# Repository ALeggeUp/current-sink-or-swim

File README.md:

# Current Sink or Swim (CSOS)

Project work from The Online Electronics Aprenticeship program at [Contextual Electronics](https://contextualelectronics.com/)

# License

This work is licensed under the Creative Commons Attribution 4.0 International License. To view a copy of this license, visit http://creativecommons.org/licenses/by/4.0/ or send a letter to Creative Commons, PO Box 1866, Mountain View, CA 94042, USA.

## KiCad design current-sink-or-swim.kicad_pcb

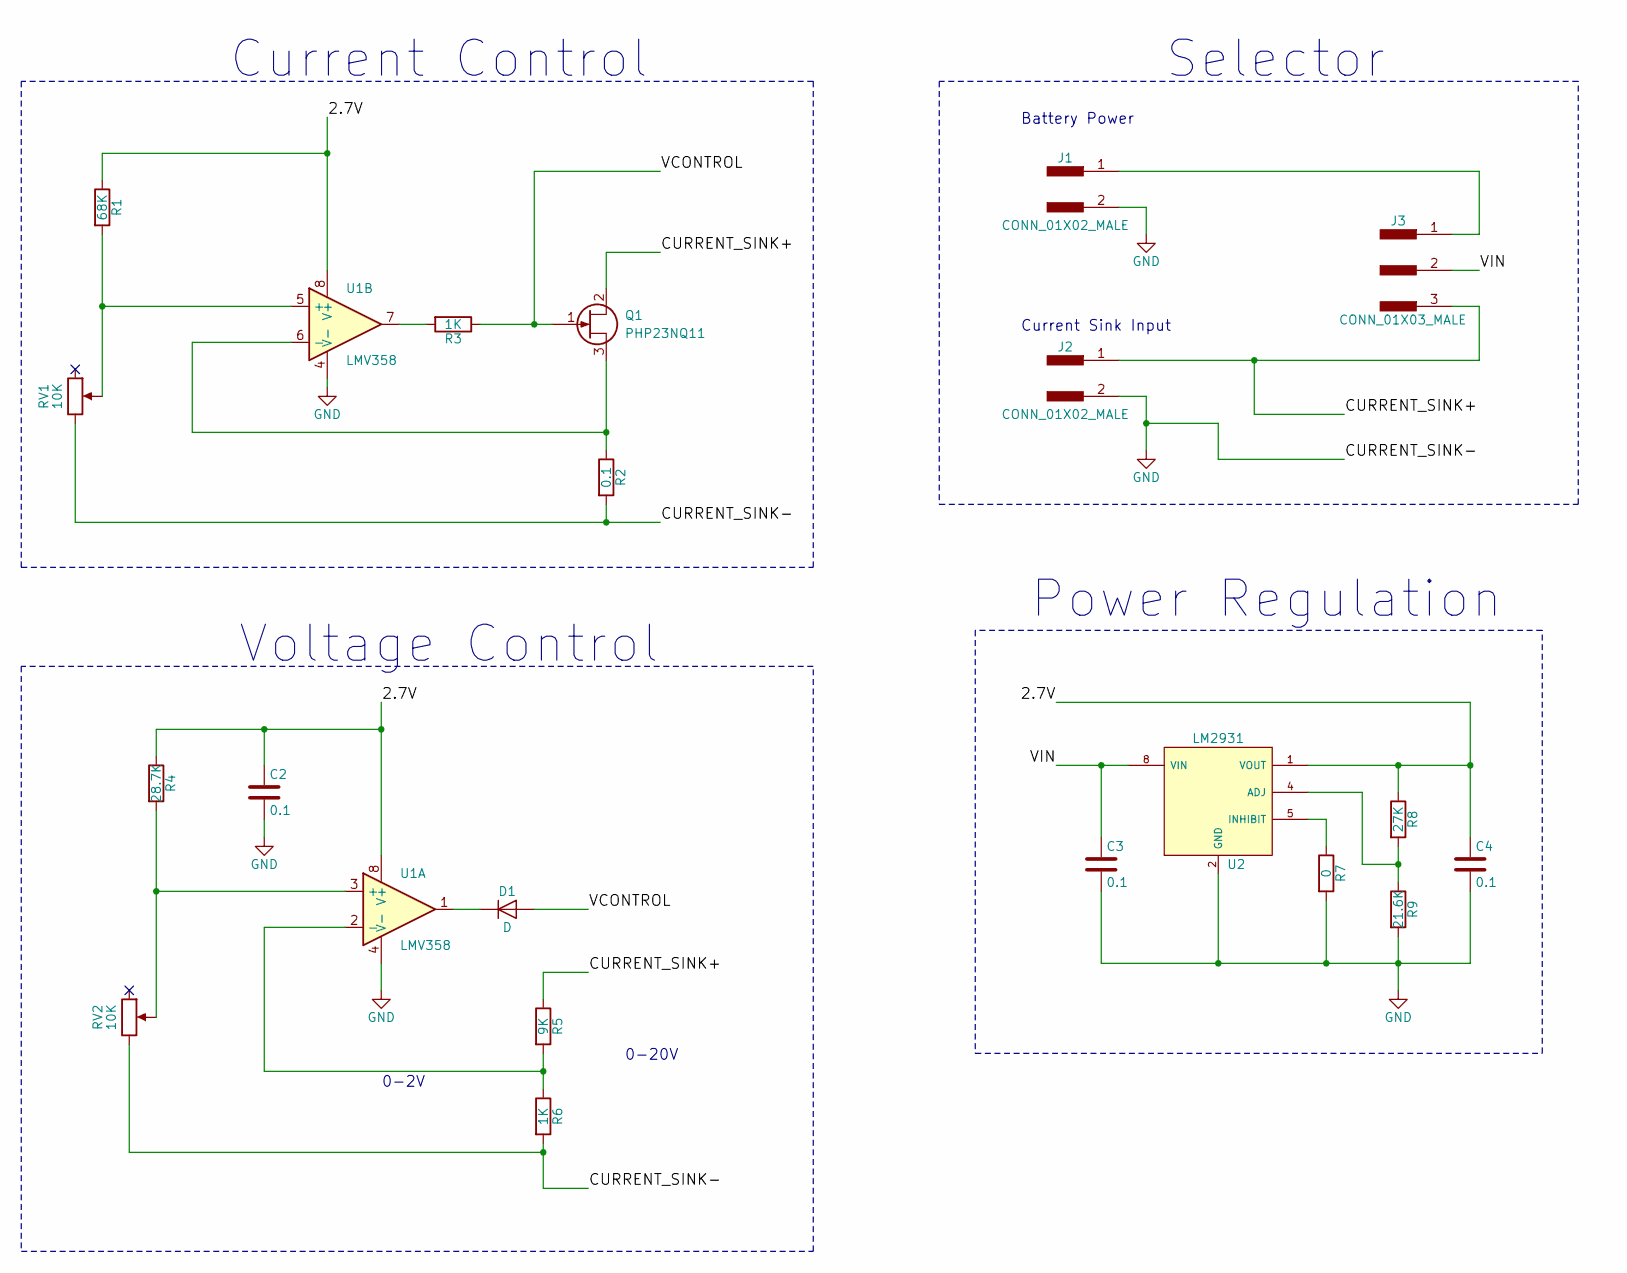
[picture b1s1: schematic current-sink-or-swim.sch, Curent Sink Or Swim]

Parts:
C2, C3, C4: 0.1; C_0805_HandSoldering
D1: D; D_SOD-123; MPN 1N4148W-TP
J1, J2: CONN_01X02_MALE; TerminalBlock_Pheonix_PT-5mm_2pol; MPN 1792863
J3: CONN_01X03_MALE; Pin_Header_Straight_1x03_Pitch2.54mm
Q1: PHP23NQ11; TO-220_Vertical; MPN PHP23NQ11T,127
R1: 68K; R_0805_HandSoldering; MPN RC0805JR-0768KL
R2: 0.1; R_Axial_DIN0414_L11.9mm_D4.5mm_P15.24mm_Horizontal; MPN AC01000001007JA100
R3, R6: 1K; R_0805_HandSoldering; MPN RC0805JR-071KL
R4: 28.7K; R_0805_HandSoldering; MPN RC0805FR-0728K7L
R5: 9K; R_0805_HandSoldering; MPN RC0805FR-079K09L
R7: 0; R_0805_HandSoldering; MPN RC0805JR-070RL
R8: 27K; R_0805_HandSoldering; MPN RC0805FR-0727KL
R9: 21.6K; R_0805_HandSoldering; MPN RC0805FR-0721K5L
RV1, RV2: 10K; P090L-02F25BR10K
U1: LMV358; SOIC-8_3.9x4.9mm_Pitch1.27mm
U2: LM2931; SOIC-8_3.9x4.9mm_Pitch1.27mm; MPN LM2931CDR2G

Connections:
/2.7V: C2.1, C4.1, R1.1, R4.1, R8.1, U1.8 (V+), U2.1 (VOUT); also elsewhere on the board
/CURRENT_SINK+: J2.1, J3.3, Q1.2 (D), R5.1
/VCONTROL: D1.2 (A), Q1.1 (G), R3.1
/VIN: C3.1, J3.2, U2.8 (VIN)
GND: C2.2, C3.2, C4.2, J1.2, J2.2, R2.2, R6.2, R7.2, R9.2, RV1.3, RV2.3, U1.4 (V-), U2.2 (GND), U2.3 (GND), U2.6 (GND), U2.7 (GND); also elsewhere on the board
unnamed: D1.1 (K), U1.1
unnamed: J1.1, J3.1
unnamed: Q1.3 (S), R2.1, U1.6 (-)
unnamed: R1.2, RV1.2, U1.5 (+)
unnamed: R3.2, U1.7
unnamed: R4.2, RV2.2, U1.3 (+)
unnamed: R5.2, R6.1, U1.2 (-)
unnamed: R7.1, U2.5 (INHIBIT)
unnamed: R8.2, R9.1, U2.4 (ADJ)

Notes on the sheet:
Current Sink Input
Battery Power
Power Regulation
Current Control
Voltage Control
Selector
0-20V
0-2V

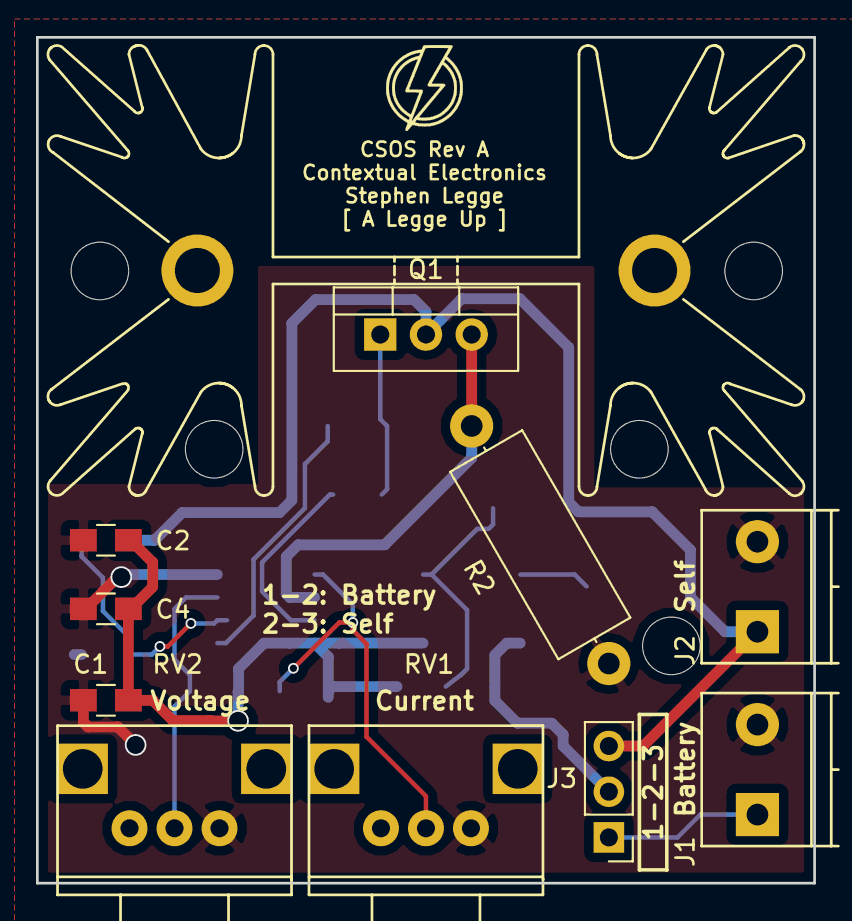
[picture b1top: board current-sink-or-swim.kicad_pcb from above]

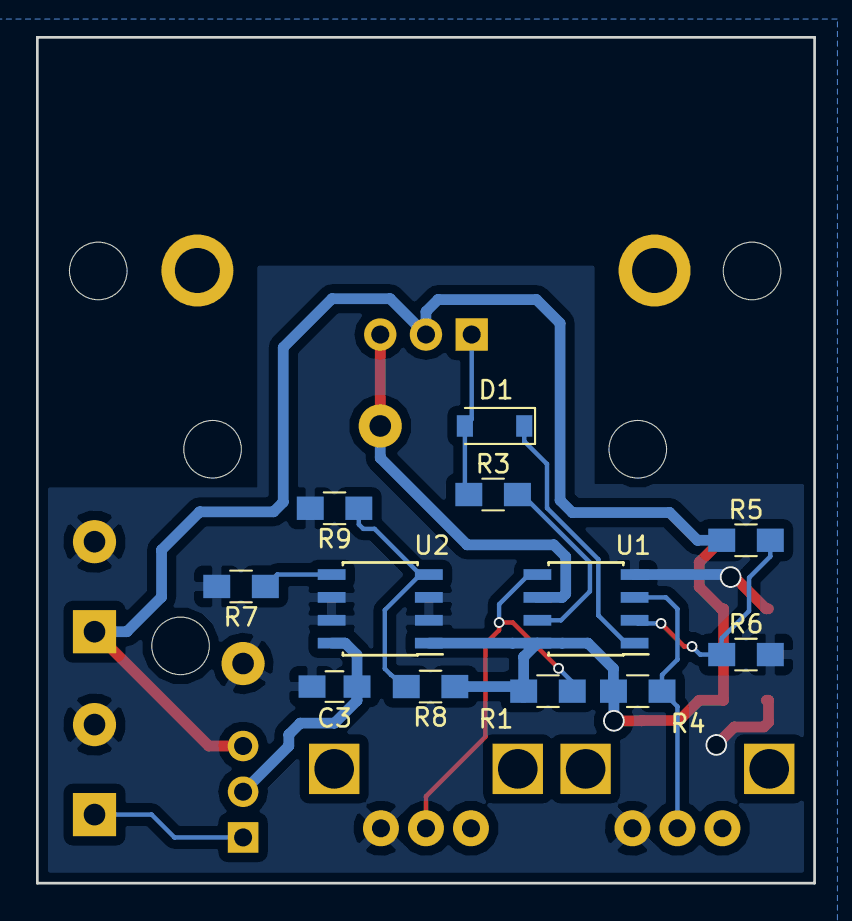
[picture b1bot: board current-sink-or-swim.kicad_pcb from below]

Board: 2 copper layers, 43.2 x 47.0 mm, 22 parts (12 on the bottom side), 14 nets.

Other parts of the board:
C1: C; C_0805_HandSoldering

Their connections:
/2.7V: C1.1; also elsewhere on the board
GND: C1.2; also elsewhere on the board

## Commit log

2017-05-19 Added license file and updated readme
2017-05-19 Initial commit of the KiCad project files
2017-05-19 Screenshot of project summary as a reminder
2017-05-19 Symbols created for CSOS project (op-amp and voltage regulator)
2017-05-19 Project save moved [general] section for some reason
2017-05-19 Insert new local libraries at the top of the list
2017-05-19 Schematic capture to match up with CSOS Project step
    "Creating the Initial CSOS Schematic" at CE
2017-05-19 Corrected TC1016 to have the correct pins
2017-05-19 Moved some things around and added some MPN's where known
2017-05-19 Datasheet for TC1016
2017-05-19 Add reference to datasheet for TC1016
2017-05-20 Added LM2931 linear regulator schematic symbol to local library
2017-05-20 Added voltage control and reorganized/cleaned up the page
2017-05-20 Annotated schematic automatically and then made some manual tweaks
2017-05-20 Changed background of IC schematic symbol to be filled to match the KLC
2017-05-20 Added metadata for components and links to datasheets
2017-05-22 Added heatsink and updated to correct FET symbol
2017-05-22 Datasheets for terminal blocks, heatsink and potentiometer
2017-06-15 Added part metadata to the schematic for BOM
2017-06-15 Removed pin that was standing in as heatsink
2017-06-15 Layout of board as ordered
2017-06-15 Footprints created for CSOS
2017-06-15 Image used as "logo" on the board
